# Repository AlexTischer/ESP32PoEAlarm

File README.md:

# ESP32 PoE Alarm Board

This repository contains all files related to the ESP32-Alarm board project.

## Project Structure

- **Docs/**  
  Project documentation (LaTeX sources, images, generated PDFs, etc.).

- **Resources/**  
  Manuals, datasheets, reference images, and other useful materials.

- **alarm.yaml**  
  Main ESPHome configuration file, defining the firmware behavior for the ESP32.

- **Case v2.step**  
  3D model of the enclosure for the board.

- **ESP32_Alarm_PCB.kicad_sch**  
  Electrical schematic of the board, created with KiCad.

- **ESP32_Alarm_PCB.kicad_pcb**  
  PCB layout of the board, created with KiCad.

- **ESP32_Alarm_PCB.kicad_pro / .kicad_prl / .kicad_dru**  
  KiCad project files and design rule settings.

- **ESP32_Alarm_PCB.step**  
  3D model of the PCB for mechanical integration and visualization.

- **production/**  
  Folder containing production files such as netlists and fabrication archives.

- **ESP32-POE/**  
  Custom KiCad libraries, footprints, and symbols, including modules and screw terminals.

- **ESP32_Alarm_PCB-backups/**  
  Automatic backups of KiCad project files.

- **fabrication-toolkit-options.json**  
  Options for PCB fabrication toolkit and production file generation.

## Notes

- All KiCad project files are compatible with version 8.0 or newer.
- To build and upload the firmware, edit and use `alarm.yaml` with ESPHome.

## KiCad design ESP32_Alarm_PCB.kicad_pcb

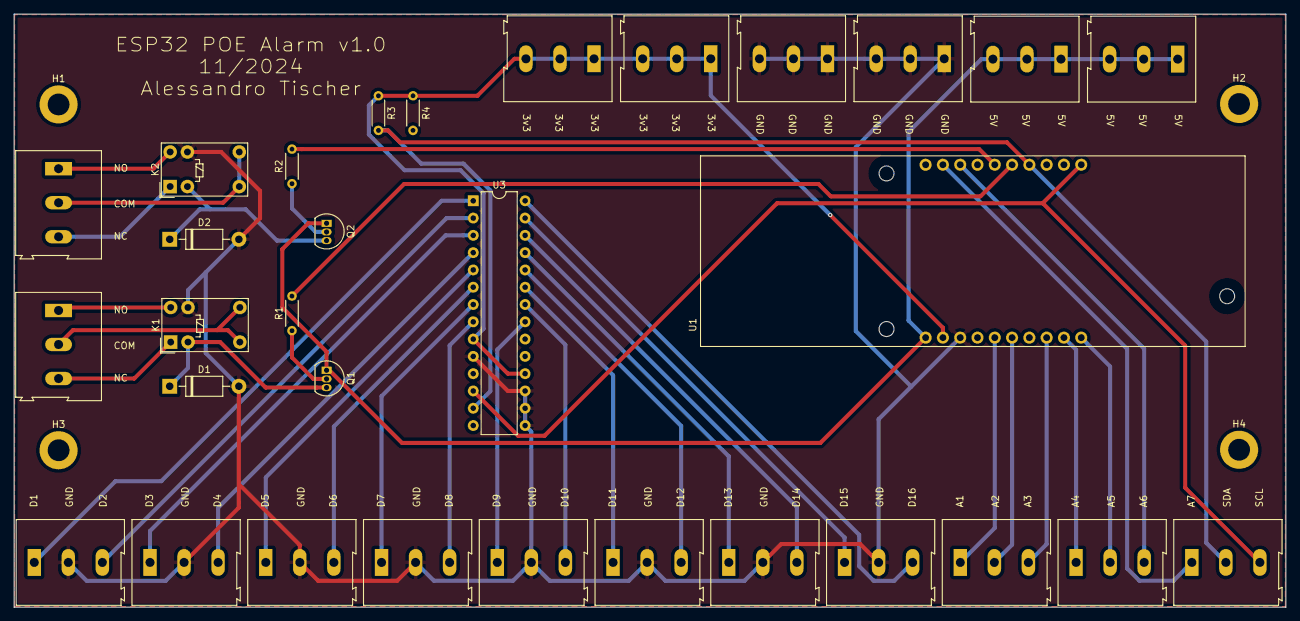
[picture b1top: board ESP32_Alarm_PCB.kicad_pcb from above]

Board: 2 copper layers, 186.8 x 87.1 mm, 35 parts (0 on the bottom side), 40 nets.

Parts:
D1, D2: 1N4007; D_DO-41_SOD81_P10.16mm_Horizontal
H1, H2, H3, H4: MountingHole; MountingHole_3.2mm_M3_DIN965_Pad
J1, J2, J3, J4, J5, J6, J7, J8, J9, J10, J11, J12, J13, J14, J15, J16, J17, J18, J19: Screw_Terminal_01x03; ScrewTerminal
K1, K2: G5V-1; Relay_SPDT_Omron_G5V-1
Q1, Q2: BC547; TO-92L_Inline
R1, R2: 1000; R_Axial_DIN0204_L3.6mm_D1.6mm_P5.08mm_Horizontal
R3, R4: 2200; R_Axial_DIN0204_L3.6mm_D1.6mm_P5.08mm_Horizontal
U1: ESP32-POE; MODULE_ESP32-POE
U3: MCP23017_SP; DIP-28_W7.62mm

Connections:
+3.3V: J16.1, J16.2, J16.3, J17.1, J17.2, J17.3, R3.1, R4.1, U1.EXT1_2 (+3.3V), U3.9 (VDD), U3.18 (~RESET)
+5V: J12.1, J12.2, J12.3, J13.1, J13.2, J13.3, Q1.1 (C), Q2.1 (C), U1.EXT1_1 (+5V)
GND: D1.2 (A), D2.2 (A), J1.2, J2.2, J3.2, J4.2, J5.2, J6.2, J7.2, J8.2, J14.1, J14.2, J14.3, J15.1, J15.2, J15.3, K1.9, K2.9, U1.EXT1_3 (GND), U3.10 (VSS), U3.15 (A0), U3.16 (A1), U3.17 (A2)
unnamed: D1.1 (K), K1.2, Q1.3 (E)
unnamed: D2.1 (K), K2.2, Q2.3 (E)
unnamed: J1.1, U3.1 (GPB0)
unnamed: J1.3, U3.2 (GPB1)
unnamed: J2.1, U3.3 (GPB2)
unnamed: J2.3, U3.4 (GPB3)
unnamed: J3.1, U3.5 (GPB4)
unnamed: J3.3, U3.6 (GPB5)
unnamed: J4.1, U3.7 (GPB6)
unnamed: J4.3, U3.8 (GPB7)
unnamed: J5.1, U3.21 (GPA0)
unnamed: J5.3, U3.22 (GPA1)
unnamed: J6.1, U3.23 (GPA2)
unnamed: J6.3, U3.24 (GPA3)
unnamed: J7.1, U3.25 (GPA4)
unnamed: J7.3, U3.26 (GPA5)
unnamed: J8.1, U3.27 (GPA6)
unnamed: J8.3, U3.28 (GPA7)
unnamed: J9.1, U1.EXT1_5 (GPIO0)
unnamed: J9.2, U1.EXT1_6 (GPIO1/U0TXD)
unnamed: J9.3, U1.EXT1_8 (GPIO3/U0RXD)
unnamed: J10.1, U1.EXT1_9 (GPIO4/U1TXD)
unnamed: J10.2, U1.EXT1_10 (GPIO5/SPI_CS)
unnamed: J10.3, U1.EXT2_3 (GPI35)
unnamed: J11.1, U1.EXT2_2 (GPI36/U1RXD)
unnamed: J11.2, R3.2, U1.EXT2_7 (GPIO16/I2C-SCL), U3.13 (SDA)
unnamed: J11.3, U1.EXT2_10 (GPIO13/I2C-SDA), U3.12 (SCK)
unnamed: J18.1, K1.10
unnamed: J18.2, K1.5, K1.6
unnamed: J18.3, K1.1
unnamed: J19.1, K2.10
unnamed: J19.2, K2.5, K2.6
unnamed: J19.3, K2.1
unnamed: Q1.2 (B), R1.1
unnamed: Q2.2 (B), R2.1
unnamed: R1.2, U1.EXT2_6 (GPIO32)
unnamed: R2.2, U1.EXT2_5 (GPIO33)

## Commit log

2025-05-09 Added ReadMe
